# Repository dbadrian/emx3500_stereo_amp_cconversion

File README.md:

# EMX3500 To Stereo Conversion

A "replacement" PCB for the [EMX3500](https://de.yamaha.com/files/download/other_assets/1/324571/EMX3500G.pdf) to convert the L/R-amplification stages and Graphic Equalizer (GEQ) to simple stereo amp.

## What is this project?
EMX3500 is an older analog powered mixer by Yamaha, see the below image.
This project separates the mixing part from the amp part of the original product.
To this end, a custom PCB was designed to enable the removal of all unnecessary parts (channels, tape board, various input boards...the massive chassis)

This was required as, looking at the original PCBs (>10 individual PCBs), we find that
* The original PCBs are designed using single layer PCBs with star-grounding (with some PCBs (or parts thereof) directly grounded to the chassis, others via other PCBs)
* Many of mixers PCBs have multiple sub-circuits of different functionalities and its near impossible to remove any part without breaking the complete system

Hence, my conclusion was to refactor the needed circuit paths from a plethora of individual PCBS onto new single purpose PCBs.
This creates a creates a stand-alone stereo amp and, in the future, I can restore the mixer into its own device that can be connected to any stereo amp.

This repository currently contains the KiCad project for the stereo amp related PCB, that can be connected to the original GEQ and amp stages.
The circuit is more or less the original circuit, reduced to its minimal subset required to achieve the desired functionality.
At the same time, the star-grounding is changed in favor for simple 2-layer PCB design with a ground-plane.
I know, I know, hardcore-music aficionados with their bee-wax filled capacitors will cry themselves to sleep hearing this, but I can promise you...I sleep quite comfortably despite this alteration...

Further upgrades also include a small bluetooth module.

> **Note**:
> I am anything but a professional circuit designer. In fact, this was my first complete PCB design with manufacturing...

> **Warning**:
> The headphone related part of the PCB does not what you might think, and will be completely removed/changed in a future revision of this project.

## Why did you destroy a mixer? Why thou!?
By chance I got my hands on a fully-working EMX-3500 for 20EUR at an auction.
I did ***not expect*** this mixer to work at all, but to my surprise all 16-channels, GEQ, DSP board, etc all worked without a hiccup (except maybe slowly deteriorated pots...)
However, I bought it with the intention for salvaging parts for synth-related projects, but clearly this would have been a crime to destroy down to individual parts.

Nevertheless the housing wasn't in the most prestine condition: screws were rusted in (previous owner seemed to have stored it in a garage for an extended time period), one channel's XLR connector was broken in.
Also, and that was the major issue: I didn't have a space for nearly a gigantic and very heavy mixer in my apartment. I didn't plan for it... I was, however, in need for a new stereo amp :).
And the mixer part still exists as is and will be rebuilt into a smaller, independent unit.

## Before and after

The case is not totally finished and a temporary housing.
All metal parts are properly grounded.

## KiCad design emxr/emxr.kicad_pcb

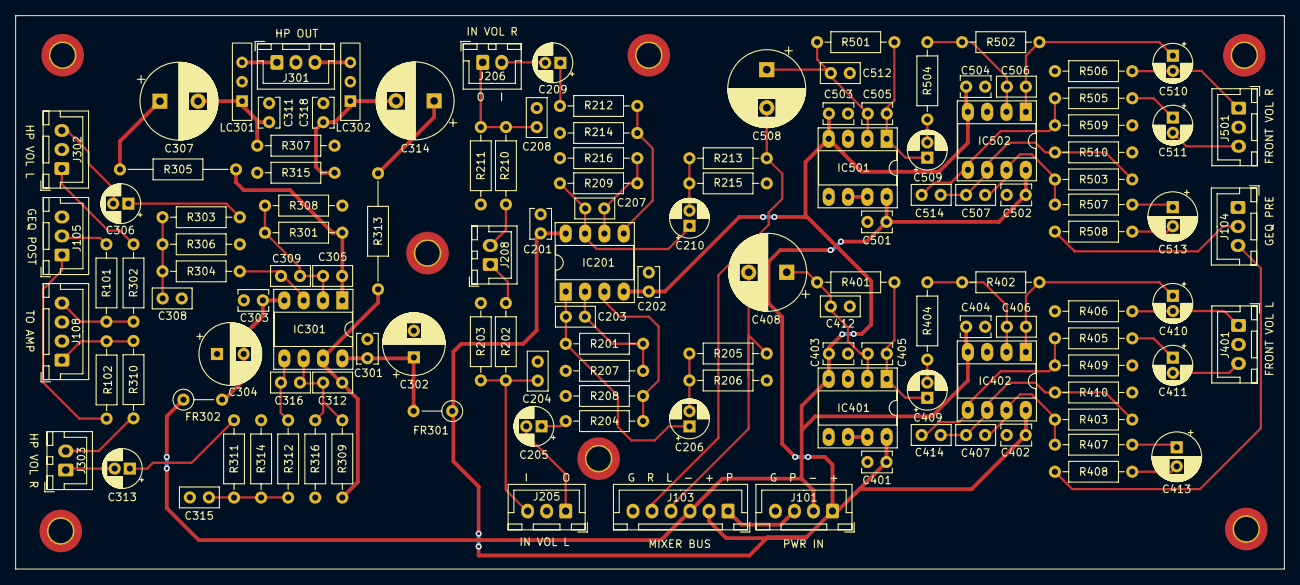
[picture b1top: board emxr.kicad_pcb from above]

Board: 2 copper layers, 166.7 x 72.7 mm, 138 parts (0 on the bottom side), 78 nets.

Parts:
C201, C202, C401, C402, C403, C404, C501, C502, C503, C504: 0.01; C_Disc_D3.8mm_W2.6mm_P2.50mm
C203, C204, C207, C208, C305, C308, C309, C312, C315, C316, C414, C514: 100p; C_Disc_D5.0mm_W2.5mm_P2.50mm
C205, C206, C209, C210, C306, C313, C409, C410, C411, C509, C510, C511: 22/50; CP_Radial_D5.0mm_P2.00mm
C301, C303: 0.1; C_Disc_D3.8mm_W2.6mm_P2.50mm
C302, C304: 100/25; CP_Radial_D8.0mm_P3.50mm
C307, C314, C408, C508: 220/25; CP_Radial_D10.0mm_P5.00mm
C311, C318: 0.001; C_Disc_D3.8mm_W2.6mm_P2.50mm
C405, C505: 47p; C_Disc_D3.8mm_W2.6mm_P2.50mm
C406, C407, C506, C507: 150p; C_Disc_D5.0mm_W2.5mm_P2.50mm
C412, C512: 220p; C_Disc_D5.0mm_W2.5mm_P2.50mm
C413, C513: 47/50; CP_Radial_D6.3mm_P2.50mm
FR301, FR302: 10 1/4; R_Axial_DIN0207_L6.3mm_D2.5mm_P5.08mm_Vertical
H101, H102, H103, H104, H105, H106, H107: MH; MountingHole_3.2mm_M3_DIN965_Pad_TopBottom
IC201: NJM4558D; DIP-8_W7.62mm_Socket_LongPads
IC301: NJM4556D; DIP-8_W7.62mm_Socket_LongPads
IC401, IC501: NJM2068DD; DIP-8_W7.62mm_Socket_LongPads
IC402, IC502: NJM4580; DIP-8_W7.62mm_Socket_LongPads
J101: POWER; JST_XH_B4B-XH-A_1x04_P2.50mm_Vertical
J103: Bus Conn; JST_XH_B6B-XH-A_1x06_P2.50mm_Vertical
J104: GEQ_PRE; JST_XH_B3B-XH-A_1x03_P2.50mm_Vertical
J105: GEQ_POST; JST_XH_B3B-XH-A_1x03_P2.50mm_Vertical
J108: AUDIO_OUT; JST_XH_B4B-XH-A_1x04_P2.50mm_Vertical
J205: InpVolL; JST_XH_B3B-XH-A_1x03_P2.50mm_Vertical
J206: InpVolR; JST_XH_B2B-XH-A_1x02_P2.50mm_Vertical
J208: SrcSel; JST_XH_B2B-XH-A_1x02_P2.50mm_Vertical
J301: HPHONES; JST_XH_B3B-XH-A_1x03_P2.50mm_Vertical
J302: HPVolL; JST_XH_B3B-XH-A_1x03_P2.50mm_Vertical
J303: HPVolR; JST_XH_B2B-XH-A_1x02_P2.50mm_Vertical
J401, J501: FrontVolL; JST_XH_B3B-XH-A_1x03_P2.50mm_Vertical
LC301, LC302: 270p; LCL_EMX
R101, R102, R408, R508: 10; R_Axial_DIN0207_L6.3mm_D2.5mm_P10.16mm_Horizontal
R201, R209, R410, R510: 15k; R_Axial_DIN0207_L6.3mm_D2.5mm_P10.16mm_Horizontal
R202, R204, R210, R212, R302, R310, R405, R505: 100; R_Axial_DIN0207_L6.3mm_D2.5mm_P10.16mm_Horizontal
R203, R206, R211, R215, R409, R509: 47k; R_Axial_DIN0207_L6.3mm_D2.5mm_P10.16mm_Horizontal
R205, R213, R401, R501: 27k; R_Axial_DIN0207_L6.3mm_D2.5mm_P10.16mm_Horizontal
R207, R216, R301, R308, R309, R316, R402, R404, R502, R504: 10k; R_Axial_DIN0207_L6.3mm_D2.5mm_P10.16mm_Horizontal
R208, R214, R306, R314: 18k; R_Axial_DIN0207_L6.3mm_D2.5mm_P10.16mm_Horizontal
R303, R304, R311, R312: 220; R_Axial_DIN0207_L6.3mm_D2.5mm_P10.16mm_Horizontal
R305, R313: 100/1W; R_Axial_DIN0207_L6.3mm_D2.5mm_P15.24mm_Horizontal
R307, R315, R406, R506: 100k; R_Axial_DIN0207_L6.3mm_D2.5mm_P10.16mm_Horizontal
R403, R503: 11k; R_Axial_DIN0207_L6.3mm_D2.5mm_P10.16mm_Horizontal
R407, R507: 330; R_Axial_DIN0207_L6.3mm_D2.5mm_P10.16mm_Horizontal

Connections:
+15V: C201.2, C401.2, C402.2, C501.2, C502.2, FR301.1, IC201.8 (V+), IC401.8 (V+), IC402.8 (V+), IC501.8 (V+), IC502.8 (V+), J101.1, J103.2
-15V: C202.1, C403.1, C404.1, C503.1, C504.1, FR302.1, IC201.4 (V-), IC401.4 (V-), IC402.4 (V-), IC501.4 (V-), IC502.4 (V-), J101.2, J103.3
/Stereo Channel L/POT_FRONT_VOL_L_POST: C411.2, J401.3
/Stereo Channel L/POT_FRONT_VOL_L_PRE: C410.2, J401.1, R406.1
/Stereo Channel R/POT_FRONT_VOL_L_POST: C511.2, J501.3
/Stereo Channel R/POT_FRONT_VOL_L_PRE: C510.2, J501.1, R506.1
BUS_L: C408.2, J103.4, R205.1
BUS_R: C508.2, J103.5, R213.1
GND: C201.1, C202.2, C204.2, C208.2, C301.1, C302.2, C303.2, C304.1, C308.2, C311.2, C315.2, C318.2, C401.1, C402.1, C403.2, C404.2, C412.2, C501.1, C502.1, C503.2, C504.2, C512.2, H101.1, H102.1, H103.1, H104.1, H105.1, H106.1, H107.1, IC401.3 (+), IC401.5 (+), IC402.3 (+), IC501.3 (+), IC501.5 (+), IC502.3 (+), J101.4, J103.6, J104.1, J105.3, J108.2, J108.3, J205.2, J301.2, J302.2, J401.2, J501.2, LC301.2, LC302.2, R203.1, R206.2, R207.2, R208.2, R211.1, R214.2, R215.2, R216.2, R306.2, R307.2, R308.2, R314.2, R315.2, R316.2, R406.2, R409.1, R410.1, R506.2, R509.1, R510.1
unnamed: C203.1, IC201.2 (-), R201.1, R207.1
unnamed: C203.2, C206.1, IC201.1, R201.2
unnamed: C204.1, J205.3, R202.1, R203.2
unnamed: C205.1, R204.1
unnamed: C205.2, J205.1
unnamed: C206.2, R205.2, R206.1
unnamed: C207.1, IC201.6 (-), R209.1, R216.1
unnamed: C207.2, C210.1, IC201.7, R209.2
unnamed: C208.1, J206.1, R210.1, R211.2
unnamed: C209.1, R212.1
unnamed: C209.2, J206.2
unnamed: C210.2, R213.2, R215.1
unnamed: C301.2, C302.1, FR301.2, IC301.8 (V+)
unnamed: C303.1, C304.2, FR302.2, IC301.4 (V-)
unnamed: C305.1, C309.2, IC301.2 (-), R301.1, R308.1
unnamed: C305.2, IC301.1, R301.2, R305.1
unnamed: C306.1, R303.1
unnamed: C306.2, J302.3
unnamed: C307.1, R305.2
unnamed: C307.2, C311.1, LC301.1, R307.1
unnamed: C308.1, R303.2, R304.1, R306.1
unnamed: C309.1, IC301.3 (+), R304.2
unnamed: C312.1, C316.2, IC301.6 (-), R309.1, R316.1
unnamed: C312.2, IC301.7, R309.2, R313.1
unnamed: C313.1, R311.1
unnamed: C313.2, J303.1
unnamed: C314.1, R313.2
unnamed: C314.2, C318.1, LC302.1, R315.1
unnamed: C315.1, R311.2, R312.1, R314.1
unnamed: C316.1, IC301.5 (+), R312.2
unnamed: C405.1, C408.1, C412.1, IC401.2 (-), R401.1
unnamed: C405.2, C409.1, IC401.1, R401.2
unnamed: C406.1, IC402.2 (-), R402.1, R404.2
unnamed: C406.2, C410.1, IC402.1, R402.2
unnamed: C407.1, C414.2, IC402.6 (-), R403.1, R410.2
unnamed: C407.2, IC402.7, R403.2, R407.1
unnamed: C409.2, R404.1
unnamed: C411.1, R405.1
unnamed: C413.1, R407.2
unnamed: C413.2, R408.1
unnamed: C414.1, IC402.5 (+), R405.2, R409.2
unnamed: C505.1, C508.1, C512.1, IC501.2 (-), R501.1
unnamed: C505.2, C509.1, IC501.1, R501.2
unnamed: C506.1, IC502.2 (-), R502.1, R504.2
unnamed: C506.2, C510.1, IC502.1, R502.2
unnamed: C507.1, C514.2, IC502.6 (-), R503.1, R510.2
unnamed: C507.2, IC502.7, R503.2, R507.1
unnamed: C509.2, R504.1
unnamed: C511.1, R505.1
unnamed: C513.1, R507.2
unnamed: C513.2, R508.1
unnamed: C514.1, IC502.5 (+), R505.2, R509.2
unnamed: IC201.3 (+), R204.2, R208.1
unnamed: IC201.5 (+), R212.2, R214.1
unnamed: IC401.6 (-), IC401.7
unnamed: IC501.6 (-), IC501.7
unnamed: J105.1, R102.1
unnamed: J105.2, R101.1
unnamed: J301.1, LC301.3
unnamed: J301.3, LC302.3
unnamed: J302.1, R302.2
unnamed: J303.2, R310.2
PHANTOM_PW: J101.3, J103.1
SELECTED_L: J208.1, R202.2
SELECTED_R: J208.2, R210.2
SINGAL_L_POST_GEQ: J108.4, R101.2, R302.1
SINGAL_L_PRE_GEQ: J104.3, R408.2
SINGAL_R_POST_GEQ: J108.1, R102.2, R310.1
SINGAL_R_PRE_GEQ: J104.2, R508.2

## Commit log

2022-07-13 add initial schematics for the new front panel pcb
2022-07-20 finish footprints, starting on component placement
2022-07-21 progress on layouting
2022-07-21 replicated layout
2022-07-21 more routing and reshuffling
2022-07-21 first pcb draft
2022-07-21 fix some missing routes in pcb
2022-07-21 change connector layout back for power
2022-07-22 finished pcb draft
2022-07-24 more cleaning up/finishing touches
2022-08-03 add bom
2022-08-03 gerbers update
2023-02-11 Add some doc
2023-02-11 readme draft
2023-02-11 readme draft/2
2023-02-11 Add some image assets
2023-02-11 add more pics
2023-02-11 update text a bit
2023-02-11 Fix filename
